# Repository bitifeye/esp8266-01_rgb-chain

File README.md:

# An RGB-Chain controlled by the ESP-01
This is an project to control a RGB-chain with the ESP-01 by WiFi.
The Esp-01 will programmed by the Arduini IDE and fit in a selfmade circuit board which will replace the old one of the RGB-chain.

## Components
To run the project you need some components. 
You find a list of them [here](https://github.com/bitifeye/esp8266-01_rgb-chain/blob/master/component_list.txt).

## Folder structure
Exery folder has its own readme for more details.
- [components](https://github.com/bitifeye/esp8266-01_rgb-chain/blob/master/component_list.txt)
  Here will you find a list of all components you need.

- [pcb](https://github.com/bitifeye/esp8266-01_rgb-chain/tree/master/pcb)
  Here will you find informations about the circuit board.

- [src](https://github.com/bitifeye/esp8266-01_rgb-chain/tree/master/src)
  In this folder is the sourcecode.
  You will also find some information how to use it.
  
## Using
Create the cuircit board by following the [instructions](https://github.com/bitifeye/esp8266-01_rgb-chain/blob/master/pcb/README.md). Programm the ESP-01 with the main.ino and stick him in the cuircit board.<br>
After that the ESP-01 will create an AP by default with name: "ESP-01". There is no password. If you are connected to the ESP-01 you can call him by "esp8266.local" form your PC. For this you have to install the [Bonjour](https://support.apple.com/bonjour), if you use an Linux-System use the [Avahi](http://avahi.org/). Calling the hostname don't work with an Android-System yet.
After calling the ESP-01 you can get the IP-Address by clicking the appropriate button. With this IP-Address you can use the system with any devices.<br>
If you set a new WiFi-connection, e.g. your own WiFi-network, the ESP-01 try to connect as a station, if that fail it create an AP agin. For that use the SSID of your network (the WiFi-name) and the matching password.<br>
For using the system by a smartphone, you have to look for the IP-Address. Either look in your router or call by your PC "esp8266.local" in your browser and click the "Get the IP-Address"-button. Now you can see the IP-Address which you can use to connect your smartphone or tablet.<br>
Make sure that the ESP-01 and the using device are both in the same network. Otherwise it will not work yet.
  
## Possible extensions of the project
- The circuit board has the opportunity to receive th IR-signal from the old remote controler.
  But the code for that aren't implemented yet.

## License
The whole project is under the GPLv3.<br>
For more ditails have a look in the [License](https://github.com/bitifeye/esp8266-01_rgb-chain/blob/master/LICENSE)

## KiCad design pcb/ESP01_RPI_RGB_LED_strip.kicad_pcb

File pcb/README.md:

## Here you get a description what you need to do to get the circuit board.

### Steps:
1.	Install "KiCad". It can be downladed here: http://kicad-pcb.org/
2.	Open KiCad and open the kicad-project. You find it in the folder "PCB" and it ends on ".pro".
3.	If you want you can change now somthing in the schematic or in the laylout.
4.	If you done, search for an provider of PCB-production. A good one is PCB-Pool (https://www.pcb-pool.com/)

	But you can choose your own. You can find a list here: https://www.mikrocontroller.net/articles/Platinenhersteller
	
	Check what kind of files (gerber-files or the pcb-files) your provider need. KiCad can also generate the gerber-files.
	If you make your order make sure that the circuit  board only has a depth of 1,0mm. Otherwise it will not fit in the control box.
5.	While your PCB is in processing you can order the components for the board. For that have a look in the [component_list.txt](https://github.com/bitifeye/esp8266-01_rgb-chain/blob/master/component_list.txt).
6.	If you have your board and the components you can solder everything on its position.
	For the connection to the RGB-LED-Chain you can use the old cabels. Unsolder the cabels from the old circuit 
7.	If you connect the cabels to the RGB-LED-Chain make sure you connect the right one to the appropriate hole.
	Do not trust the color of the cabel-isolation.

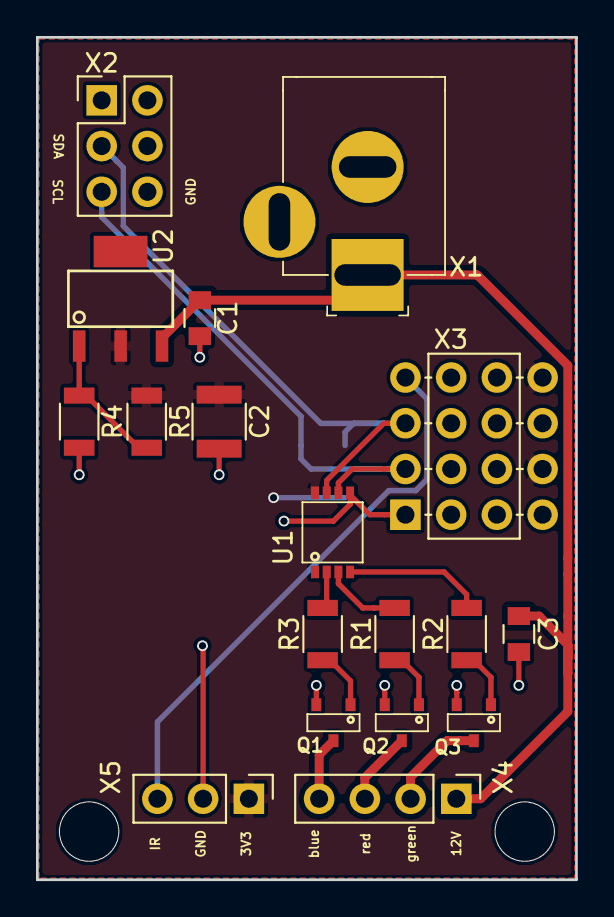
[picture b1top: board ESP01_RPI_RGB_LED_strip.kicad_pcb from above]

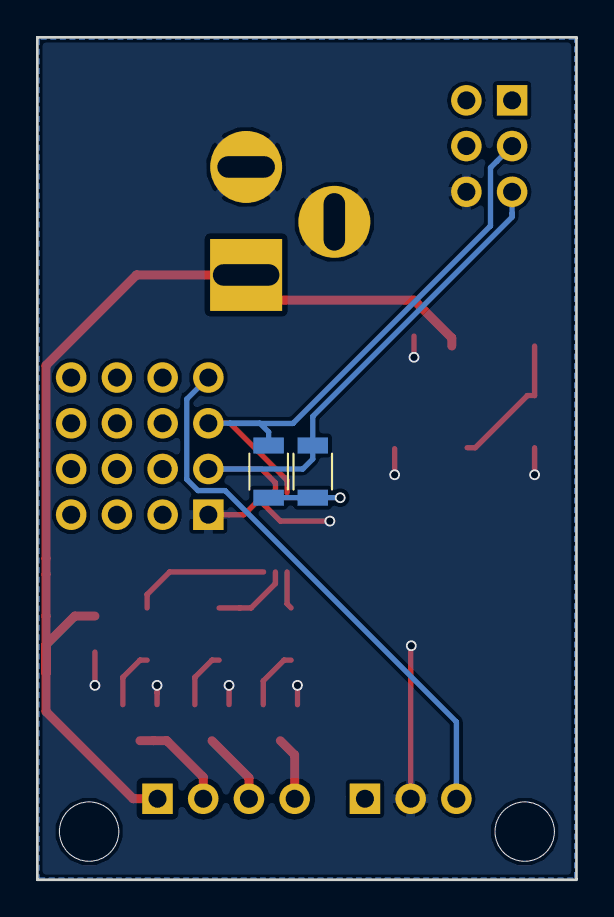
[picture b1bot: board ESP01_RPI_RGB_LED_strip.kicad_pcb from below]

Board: 2 copper layers, 29.9 x 46.8 mm, 20 parts (2 on the bottom side), 16 nets.

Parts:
C1, C3: 100n; C_0805
C2: 10u; C_1210
Q1, Q2, Q3: Si2312BDS
R1, R2, R3: 100; R_1206
R4: 0; R_1206
R5, R6, R7: No-R; R_1206
U1: PCA9633DP1
U2: LD1117A; LD1117AS33TR
X1: 1x2-Pin_Hedaer; DC-10A
X2: 2x3-Pin_Hedaer; Pin_Header_Straight_2x03_Pitch2.54mm
X3: 2x4-Pin_Hedaer; Pin_Header_Straight_For_ESP-01_2x04_Pitch2.54mm
X4: 1x4-Pin_Hedaer; Pin_Header_Straight_1x04_Pitch2.54mm
X5: 1x3-Pin_Hedaer; Pin_Header_Straight_1x03_Pitch2.54mm

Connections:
+3V3: C2.1, R5.1, R6.1, R7.1, U1.8, U2.2, X3.4, X3.8, X5.1
+12V0: C1.1, C3.1, U2.3, X1.1, X4.1
GND: C1.2, C2.2, C3.2, Q1.2, Q2.2, Q3.2, R4.2, U1.5, X1.2, X1.3, X2.6, X3.1, X5.2
IR: X3.7, X5.3
unnamed: Q1.1, R3.1
unnamed: Q2.1, R1.1
unnamed: Q3.1, R2.1
unnamed: R1.2, U1.3
unnamed: R2.2, U1.4
unnamed: R3.2, U1.2
unnamed: R4.1, R5.2, U2.1
SCL: R6.2, U1.6, X2.5, X3.3
SDA: R7.2, U1.7, X2.3, X3.5
blue: Q1.3, X4.4
green: Q3.3, X4.2
red: Q2.3, X4.3

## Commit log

2017-08-17 added pcb
    added the necessary files for the pcb
2017-08-17 added the readme for the pcb
    here are the necessary steps to take if someone want to use the pcb
2017-08-17 whitespace changes
2017-08-17 added header
2017-08-17 give some informations
2017-08-17 added the needed components
2017-08-17 added component list information
2017-08-17 added the source folder
2017-08-17 added the necessary informations
2017-08-17 added some links
2017-08-17 added the pictures
2017-08-17 added possible extesions
2017-08-17 added information to downlad the pcb folder
2017-08-18 made a closer look for that
2017-08-18 closer look for the settings
2017-08-18 give all important things a closer look
2017-08-18 unnecessary
2017-08-18 added links to the folders
2017-08-18 added pictures
2017-08-18 some whitespace changes
2017-08-18 linked the componend list
2017-08-18 added some pictures an links
2017-08-18 added picture and links
    added picture and links for the the board manager setup
2017-08-21 added using
    describe how to use the running programm
